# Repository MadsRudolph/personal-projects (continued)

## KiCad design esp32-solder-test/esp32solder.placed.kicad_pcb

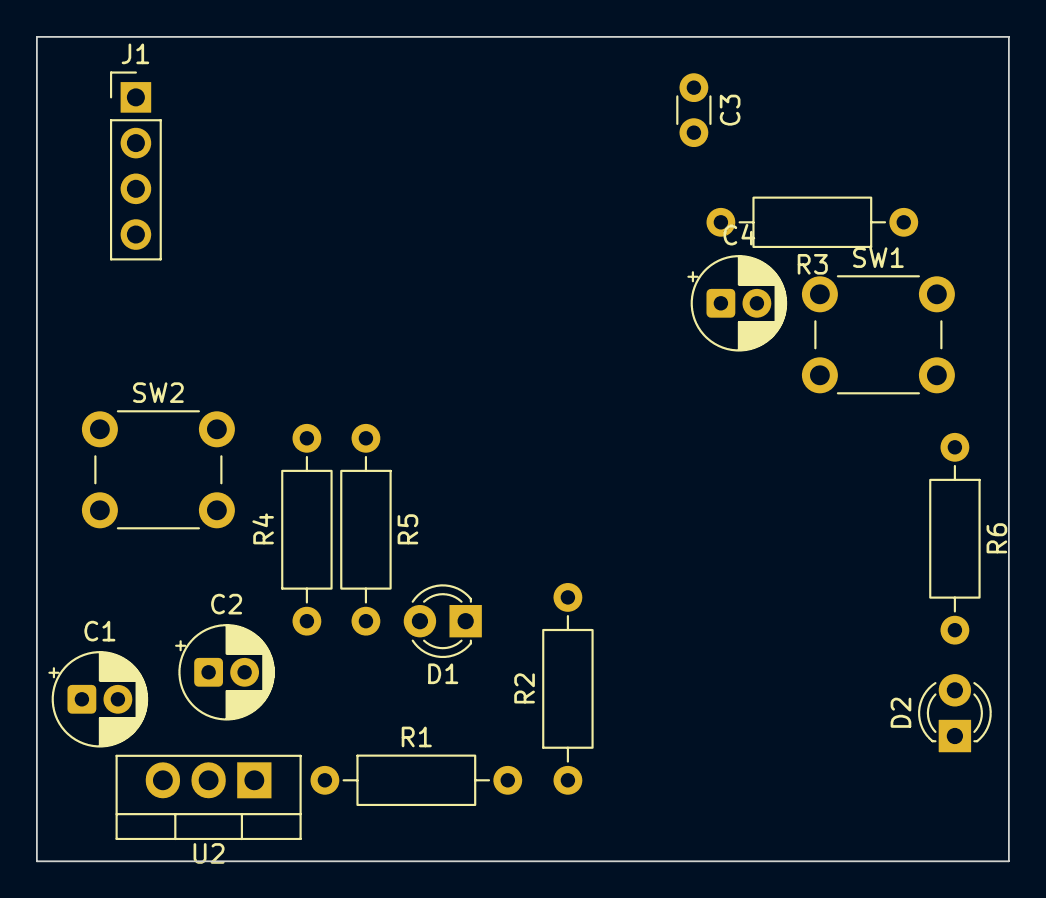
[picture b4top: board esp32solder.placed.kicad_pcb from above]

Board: 2 copper layers, 54.0 x 45.8 mm, 17 parts (1 on the bottom side), 11 nets, no tracks yet.

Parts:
C1, C2: 10u; CP_Radial_D5.0mm_P2.00mm
C3: 100n; C_Disc_D3.0mm_W1.6mm_P2.50mm
C4: 1u; CP_Radial_D5.0mm_P2.00mm
D1: LED green; LED_D3.0mm
D2: LED red; LED_D3.0mm
J1: UART / 5V; PinHeader_1x04_P2.54mm_Vertical
R1: 243; R_Axial_DIN0207_L6.3mm_D2.5mm_P10.16mm_Horizontal
R2: 392; R_Axial_DIN0207_L6.3mm_D2.5mm_P10.16mm_Horizontal
R3, R4: 10k; R_Axial_DIN0207_L6.3mm_D2.5mm_P10.16mm_Horizontal
R5: 332; R_Axial_DIN0207_L6.3mm_D2.5mm_P10.16mm_Horizontal
R6: 1k; R_Axial_DIN0207_L6.3mm_D2.5mm_P10.16mm_Horizontal
SW1: RESET; SW_PUSH_6mm
SW2: BOOT; SW_PUSH_6mm
U1: ESP32-WROOM-32; ESP32-WROOM-32_NoVias
U2: LM317T; TO-220-3_Vertical

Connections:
+3V3: C2.1, C3.1, R1.1, R3.1, R4.1, R6.1, U1.2, U2.2
/+5V_IN: C1.1, J1.2, U2.3
/IO0: R4.2, SW2.2, U1.25
/RXD0: J1.4, U1.34
/TXD0: J1.3, U1.35
GND: C1.2, C2.2, C3.2, C4.2, D1.1, D2.1, J1.1, R2.2, SW1.1, SW2.1, U1.1, U1.15, U1.38, U1.39
unnamed: D1.2, R5.2
unnamed: D2.2, R6.2
unnamed: C4.1, R3.2, SW1.2, U1.3
unnamed: R5.1, U1.24
unnamed: R1.2, R2.1, U2.1

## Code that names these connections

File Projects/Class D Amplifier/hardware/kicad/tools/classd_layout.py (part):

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sh.seg((G(74), G(33)), (G(74), G(42)))                  # follower loop, below
sh.seg((G(74), G(42)), (G(58), G(42)))
sh.seg((G(58), G(42)), U1A.pin("-"))
sh.label((G(82), G(33)), "VGND")
sh.note((G(14), G(72)), "6 V = 12 V / 2, buffered, so every stage shares "
                        "one quiet reference.", size=1.27)

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sh.seg(RV1.pin("2"), U1B.pin("-"))
sh.seg(U1B.pin("-"), (G(114), G(42)))                   # integrating cap, below
sh.seg((G(114), G(42)), C12.pin("1"))
sh.seg(U1B.pin("out"), (G(139), G(29)))                 # TRI run
sh.seg((G(130), G(29)), (G(130), G(42)))
sh.seg(C12.pin("2"), (G(130), G(42)))
sh.label((G(136), G(29)), "TRI")
TP1 = sh.place(TP, "TP1", at=(G(134), G(23)))
sh.seg((G(134), G(29)), TP1.pin("1"))

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
# 6 V reference into both stages
sh.seg(U1B.pin("+"), (G(108), G(27)))
sh.label((G(108), G(27)), "VGND")
sh.seg(U2.pin("-"), (G(152), G(33)))
sh.seg((G(152), G(33)), (G(152), G(40)))
sh.label((G(152), G(40)), "VGND")

sh.note((G(90), G(68)), "f = Vsw / (8 R C):  R4+RV1 ~ 5k6 with C12 470p gives "
                        "250 kHz;  R5/R6 set the +/-2 V window about 6 V",
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RV2 = sh.place("Device:R_Potentiometer", "RV2", at=(G(42), G(103)), value="10k")
sh.seg(C3.pin("2"), RV2.pin("1"))
sh.seg(RV2.pin("3"), (G(42), G(112)))
sh.label((G(42), G(112)), "VGND")

U1C = sh.place(OP, "U1", unit=3, at=(G(62), G(105)), value="TL074")
sh.seg(RV2.pin("2"), (G(56), G(103)))
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sh.seg((G(74), G(105)), (G(74), G(114)))
sh.seg((G(74), G(114)), (G(56), G(114)))
sh.seg((G(56), G(114)), U1C.pin("-"))
sh.label((G(78), G(105)), "AUDIO_P")

# unity inverter -> AUDIO_N
sh.seg((G(80), G(105)), (G(80), G(122)))
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sh.seg(U1D.pin("out"), (G(118), G(120)))
sh.seg((G(114), G(120)), (G(114), G(132)))
sh.seg(R9.pin("2"), (G(114), G(132)))
sh.label((G(118), G(120)), "AUDIO_N")
sh.seg(U1D.pin("+"), (G(92), G(118)))
sh.label((G(92), G(118)), "VGND")
sh.note((G(14), G(140)), "AUDIO_P and AUDIO_N are equal and opposite about "
                         "6 V - that is what swings the bridge both ways.",
        size=1.27)
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U4 = sh.place(CMP, "U4", at=(G(150), G(130)), value="LM311")

sh.seg((G(138), G(94)), U3.pin("+"))
sh.label((G(138), G(94)), "AUDIO_P")
sh.seg((G(138), G(128)), U4.pin("+"))
sh.label((G(138), G(128)), "AUDIO_N")

sh.seg(U3.pin("-"), (G(136), G(98)))                    # one triangle, both '-'
sh.seg((G(136), G(98)), (G(136), G(132)))
sh.seg((G(136), G(132)), U4.pin("-"))
sh.label((G(136), G(114)), "TRI")

for u, rref, y in ((U3, "R10", G(96)), (U4, "R11", G(130))):
    rp = sh.place(R, rref, at=(G(164), y - G(6)), value="1k")
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    sh.nc(u.pin("BAL"))
    sh.nc(u.pin("STRB"))

sh.label((G(182), G(96)), "PWM_A")
sh.label((G(182), G(130)), "PWM_B")
TP2 = sh.place(TP, "TP2", at=(G(176), G(88)))
sh.seg((G(176), G(96)), TP2.pin("1"))

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U5F = sh.place(INV, "U5", unit=6, at=(G(262), G(142)), value="CD4049UBE")

sh.seg((G(222), G(94)), U5A.pin("3"))
sh.label((G(222), G(94)), "PWM_A")
sh.seg(U5A.pin("2"), U5B.pin("5"))
sh.label((G(250), G(94)), "A_LO")
sh.seg(U5B.pin("4"), (G(282), G(94)))
sh.label((G(282), G(94)), "A_HI")

sh.seg((G(222), G(120)), U5C.pin("7"))
sh.label((G(222), G(120)), "PWM_B")
sh.seg(U5C.pin("6"), U5D.pin("9"))
sh.label((G(250), G(120)), "B_LO")
sh.seg(U5D.pin("10"), (G(282), G(120)))
sh.label((G(282), G(120)), "B_HI")

# the two spare sections: inputs tied off, outputs open
sh.seg(U5E.pin("11"), (G(226), G(142)))
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U6 = sh.place("Driver_FET:HIP4082xP", "U6", at=(G(60), G(190)),
              value="HIP4082IPZ")

for pin, name in (("AHI", "A_HI"), ("ALI", "A_LO"),
                  ("BHI", "B_HI"), ("BLI", "B_LO")):
    p = U6.pin(pin)
    sh.seg((G(30), p.y), p)
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sh.seg((G(100), G(182)), C6.pin("1"))
sh.seg(C6.pin("2"), (G(100), G(190)))
sh.seg(U6.pin("BHS"), (G(100), G(190)))
sh.label((G(88), G(190)), "SW_B")

# A channel bootstrap: AHB steps up over the BHB run, then D2 / C5 -> AHS
C5 = sh.place(C, "C5", at=(G(124), G(190)), value="100n")
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sh.seg((G(124), G(180)), C5.pin("1"))
sh.seg(C5.pin("2"), (G(124), G(198)))
sh.seg(U6.pin("AHS"), (G(136), G(198)))
sh.label((G(136), G(198)), "SW_A")

for pin, name in (("BHO", "G_BH"), ("BLO", "G_BL"),
                  ("ALO", "G_AL"), ("AHO", "G_AH")):
    p = U6.pin(pin)
    sh.seg(p, (G(86), p.y))
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L1 = sh.place("Device:L", "L1", at=(G(254), G(172)), rot=90, value="15u")
L2 = sh.place("Device:L", "L2", at=(G(254), G(188)), rot=90, value="15u")
sh.seg((G(244), G(172)), L1.pin("1"))
sh.label((G(244), G(172)), "SW_A")
sh.seg((G(244), G(188)), L2.pin("1"))
sh.label((G(244), G(188)), "SW_B")

sh.seg(L1.pin("2"), (G(302), G(172)))
sh.seg(L2.pin("2"), (G(296), G(188)))
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
TP5 = sh.place(TP, "TP5", at=(G(264), G(166)))
sh.seg((G(264), G(172)), TP5.pin("1"))
sh.label((G(264), G(169)), "OUT_P")

J3 = sh.place(TERM, "J3", at=(G(306), G(172)), value="SPEAKER 4R")
sh.seg((G(296), G(188)), (G(296), G(174)))
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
